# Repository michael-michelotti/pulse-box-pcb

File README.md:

# Pulse Box PCB

KiCad 9.0 hardware designs for the [PulseBox](https://github.com/michael-michelotti/pulse-box-esp) project — a modular LED grid system with a central controller driving a dynamically reconfigurable array of 8x8 LED panels. This repo holds the schematics, board layouts, and JLCPCB manufacturing outputs for all board revisions.

This is meant as a companion to the [main PulseBox repo](https://github.com/michael-michelotti/pulse-box-esp) — see that repo for the full system overview.

---

## Controller v1 (`Pulse_Box_PCB_v1/`)

<!-- TODO: Replace with labeled photo of v1 controller board -->

Original controller, fabricated and assembled by JLCPCB. 2-layer board built around an **STM32F407VGT6** (ARM Cortex-M4, LQFP-100). Power comes in through a 5.5mm barrel jack and is regulated by a **TPSM53604RDA** 4A buck module (down to 5V), followed by an **AP2112K-3.3** LDO for the 3.3V MCU rail. LED data is level-shifted from 3.3V to 5V through a **SN74LV1T34** before driving the WS2812B chain. USB Micro-B for serial/flashing.

---

## Controller v2 (`Pulse_Box_PCB_v2/`)

<!-- TODO: Replace with labeled photo of v2 controller board -->

Redesigned controller centered on the **ESP32-S3-WROOM-1** module (WiFi, BLE, dual-core). 2-layer, 80mm x 80mm. The barrel jack is replaced with a 24V input to match the rest of the panel bus, and the buck module is swapped for a **discrete TPS54560B** design (24V→5V, 5A) with an **AP2112K-3.3** LDO for the 3.3V rail. USB-C exposes the ESP32-S3's native USB-JTAG for debug. Dual **SN74LV1T34** level shifters drive LED data north and west, and panel interconnect is 8-pin (24V, GND, RS-485 A/B, sense, LED data).

---

## Panel v1 (`Pulse_Box_Panel_v1/`)

<!-- TODO: Replace with labeled photo of panel board -->

LED panel board, 2-layer, 80mm x 80mm. Runs an **STM32G071C8** (Cortex-M0+, LQFP-48) with four USARTs — one per edge — so adjacent panels mate face-to-face with no crossover. Power mirrors the v2 controller: 24V bus in, discrete buck to 5V for the LEDs, **AP2112K-3.3** LDO for the 3.3V MCU rail. LED data routing uses two **74HC4051** 8-channel analog muxes (one for input, one for output) so any edge can be selected as the data in/out for the panel's 8x8 grid. Four JST XH 11-position edge connectors carry 24V, GND, UART TX/RX, sense, and LED data. SWD header for debug; UART bootloader available on PA2/PA3 as a recovery path.

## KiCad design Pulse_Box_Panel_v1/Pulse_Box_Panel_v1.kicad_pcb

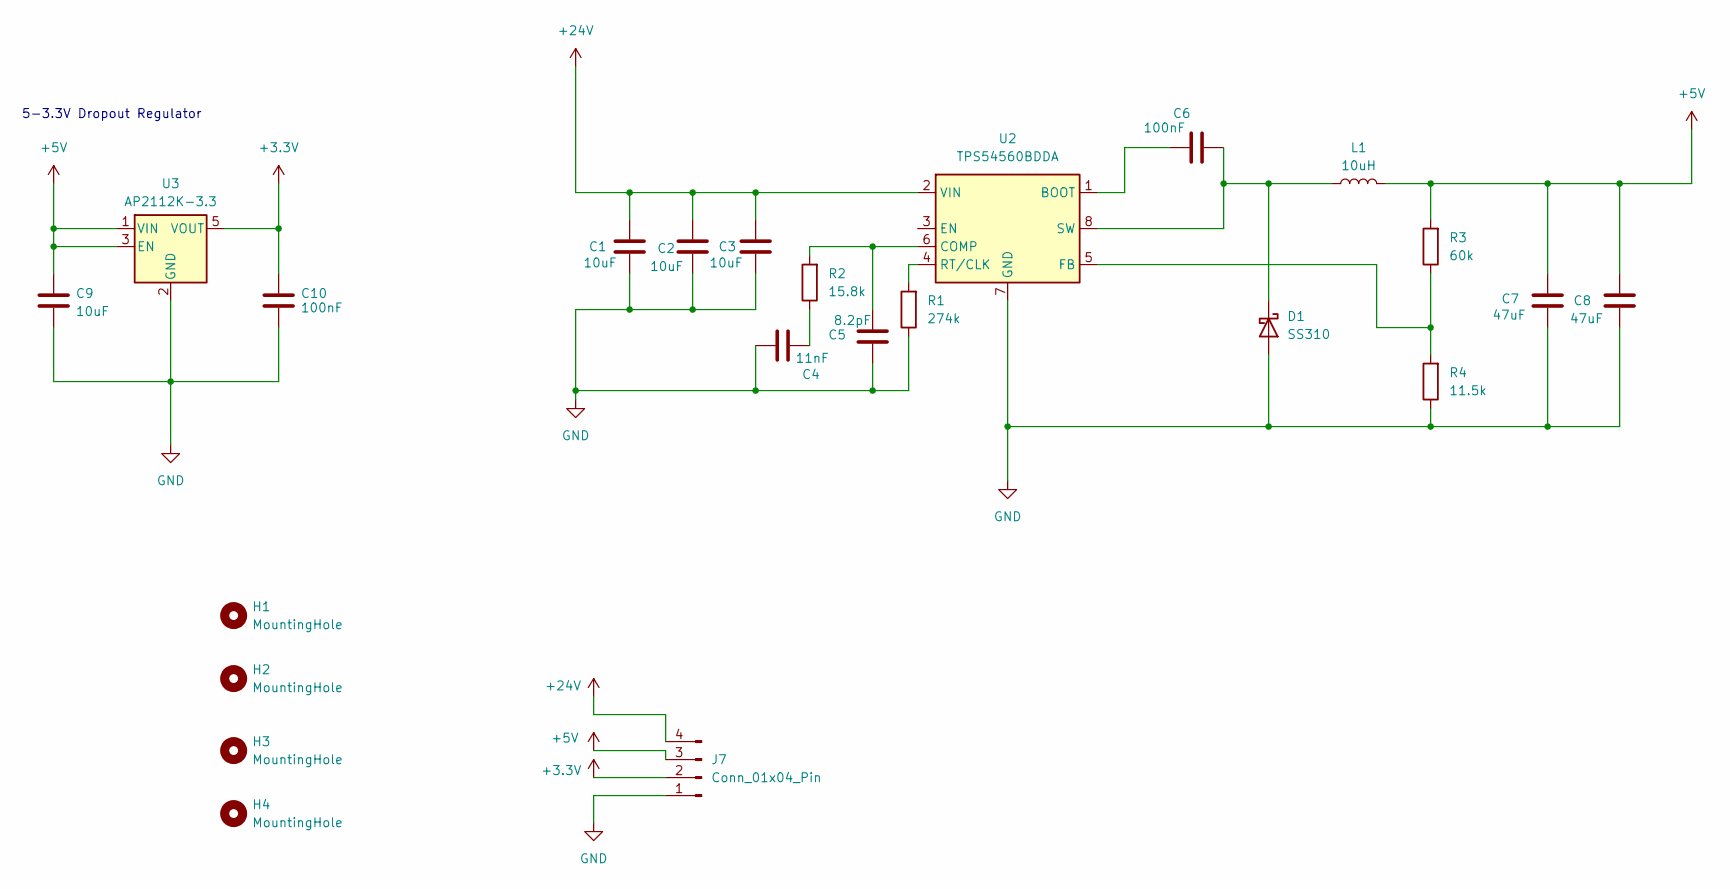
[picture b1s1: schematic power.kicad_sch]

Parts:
C1, C2, C3: 10uF; C_0805_2012Metric; JLCPCB Part # C440198
C4: 11nF; C_0805_2012Metric; JLCPCB Part # C710944
C5: 8.2pF; C_0402_1005Metric; JLCPCB Part # C1579
C6: 100nF; C_0402_1005Metric; JLCPCB Part # C1525
C7, C8: 47uF; C_0805_2012Metric; JLCPCB Part # C76636
C9: 10uF; C_0805_2012Metric; MFR PN CL21A106KAYNNNE; JLCPCB PN C15850
C10: 100nF; C_0402_1005Metric; MFR PN CL21A475KAQNNNE; JLCPCB PN C1779
D1: SS310; D_SMB; JLCPCB Part # C14651
H1, H2, H3, H4: MountingHole; MountingHole_3.2mm_M3
J7: Conn_01x04_Pin; PinHeader_1x04_P2.54mm_Vertical; JLCPCB Part # C124378
L1: 10uH; L_TechFuse_SL1040; JLCPCB Part # C22463839
R1: 274k; R_0402_1005Metric; JLCPCB Part # C27004
R2: 15.8k; R_0402_1005Metric; JLCPCB Part # C26956
R3: 60k; R_0402_1005Metric; JLCPCB Part # C25911
R4: 11.5k; R_0402_1005Metric; JLCPCB Part # C159139
U2: TPS54560BDDA; Texas_R-PDSO-G8_EP2.95x4.9mm_Mask2.4x3.1mm_ThermalVias; JLCPCB Part # C1850354
U3: AP2112K-3.3; SOT-23-5; MFR PN AP2112K-3.3; JLCPCB PN C23380830

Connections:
+3.3V: C10.1, J7.2, U3.5 (VOUT); also elsewhere on the board
+5V: C7.1, C8.1, C9.1, J7.3, L1.2, R3.2, U3.1 (VIN), U3.3 (EN); also elsewhere on the board
+24V: C1.1, C2.1, C3.1, J7.4, U2.2 (VIN); also elsewhere on the board
GND: C1.2, C2.2, C3.2, C4.1, C5.2, C7.2, C8.2, C9.2, C10.2, D1.2 (A), J7.1, R1.1, R4.1, U2.7 (GND), U2.9 (GND), U3.2 (GND); also elsewhere on the board
unnamed: C4.2, R2.1
unnamed: C6.2, D1.1 (K), L1.1, U2.8 (SW)
unnamed: C6.1, U2.1 (BOOT)
unnamed: C5.1, R2.2, U2.6 (COMP)
unnamed: R3.1, R4.2, U2.5 (FB)
unnamed: R1.2, U2.4 (RT/CLK)

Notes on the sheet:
5-3.3V Dropout Regulator

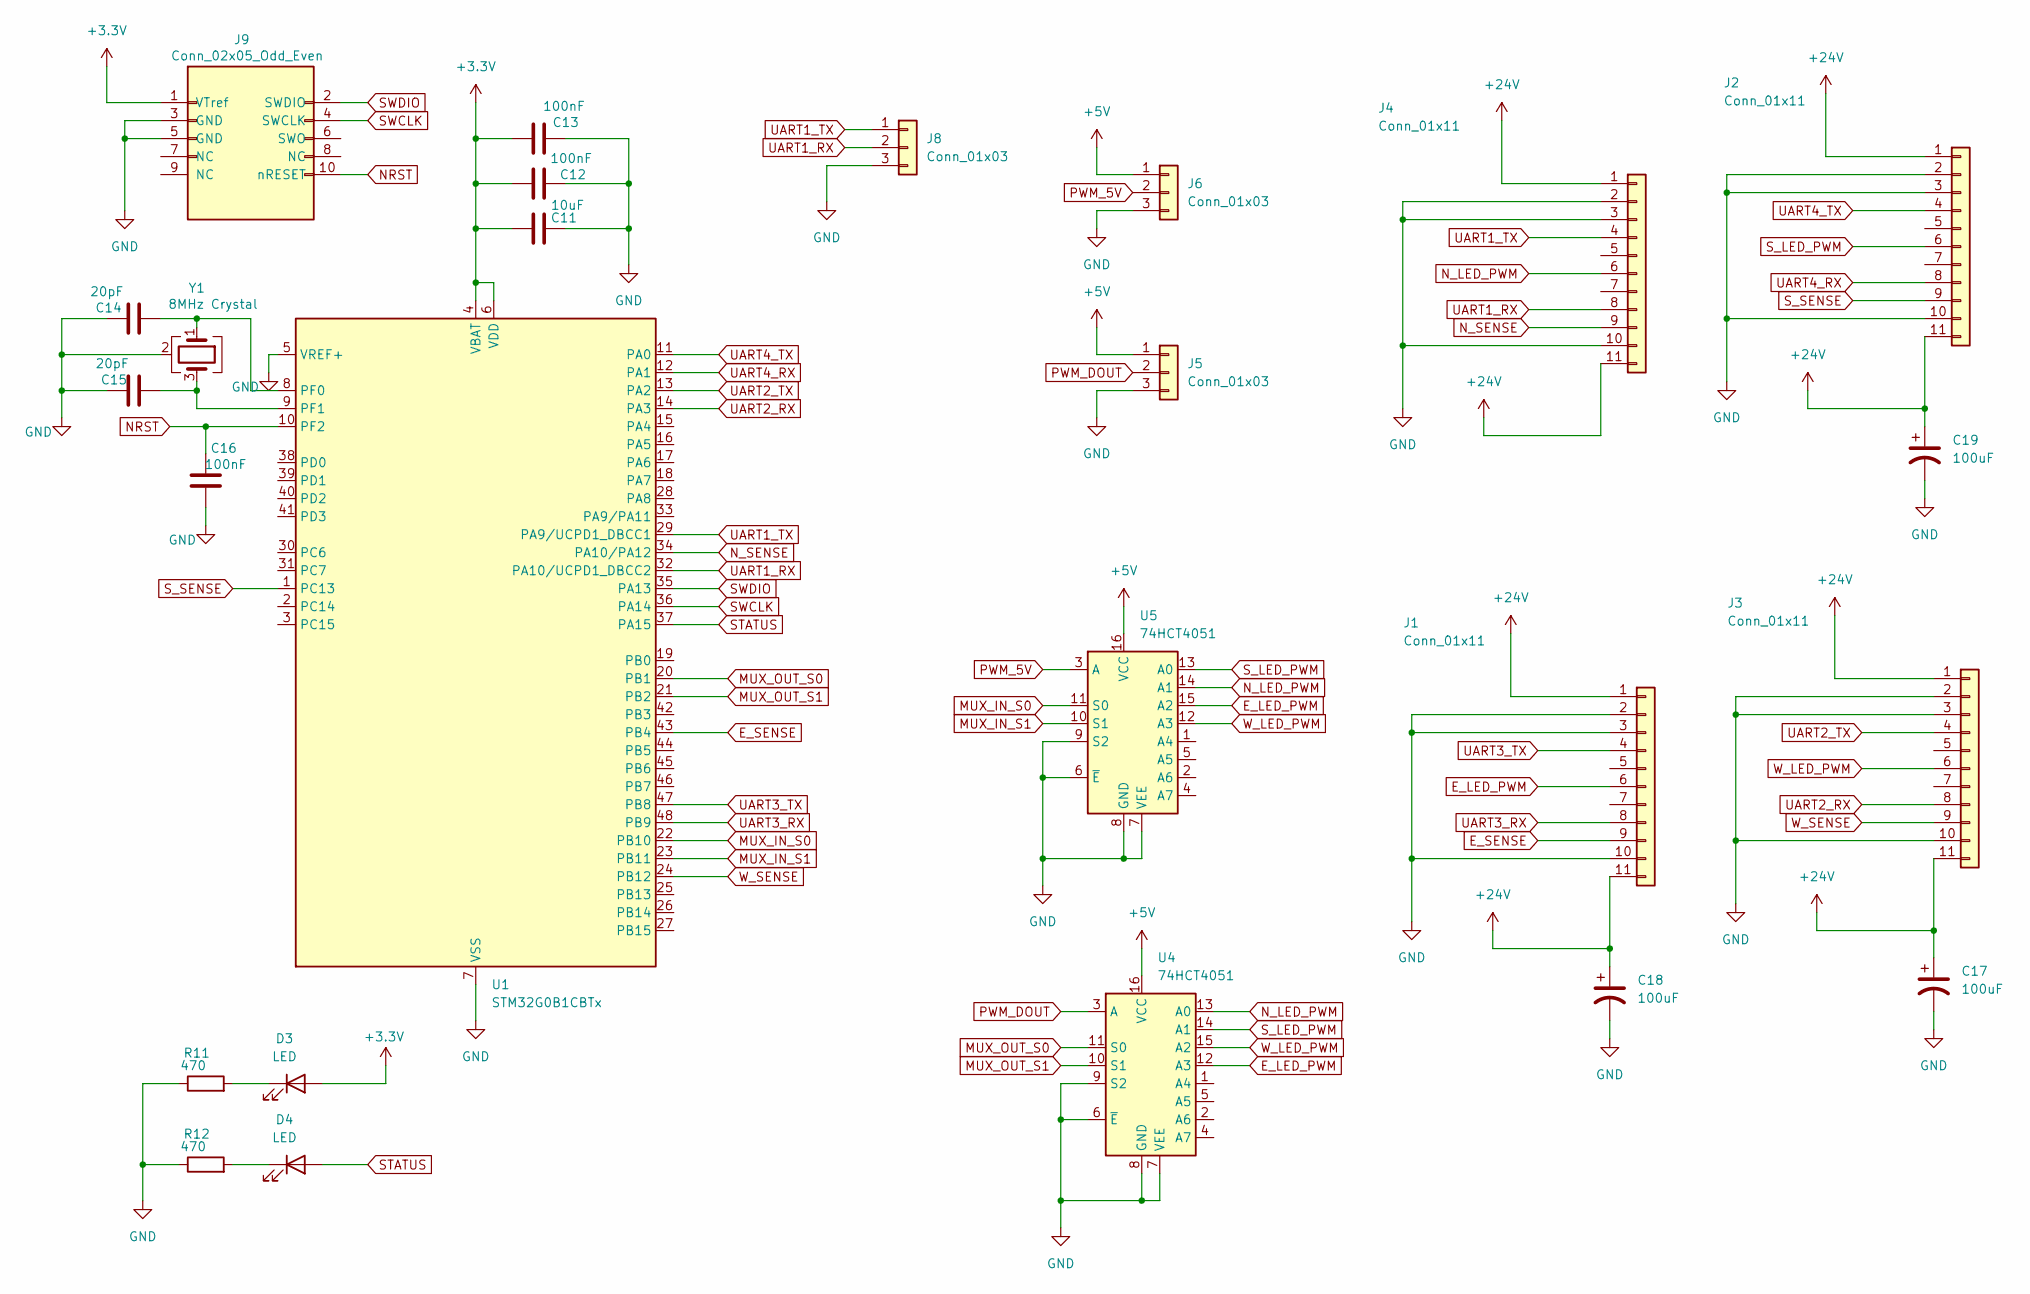
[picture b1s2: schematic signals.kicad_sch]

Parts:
C11: 10uF; C_0805_2012Metric; JLCPCB Part # C440198
C12, C13, C16: 100nF; C_0402_1005Metric; JLCPCB Part # C1525
C14, C15: 20pF; C_0402_1005Metric; JLCPCB Part # C1554
C17, C18, C19: 100uF; C_Elec_8x10.2; JLCPCB Part # C3352
D3, D4: LED; LED_0402_1005Metric; JLCPCB Part # C71911
J1, J2, J3, J4: Conn_01x11; JST_XH_B11B-XH-A_1x11_P2.50mm_Vertical; JLCPCB Part # C158031
J5, J6: Conn_01x03; JST_PH_B3B-PH-K_1x03_P2.00mm_Vertical; JLCPCB Part # C131339
J8: Conn_01x03; PinHeader_1x03_P2.54mm_Vertical; JLCPCB Part # C49257
J9: Conn_02x05_Odd_Even; PinHeader_2x05_P1.27mm_Vertical; MFR PN 20021111-00010T4LF; JLCPCB PN C239059
R11, R12: 470; R_0402_1005Metric; JLCPCB Part # C25117
U1: STM32G0B1CBTx; LQFP-48_7x7mm_P0.5mm; JLCPCB Part # C529341
U4, U5: 74HCT4051; TSSOP-16_4.4x5mm_P0.65mm; JLCPCB Part # C192055
Y1: 8MHz Crystal; Crystal_SMD_3225-4Pin_3.2x2.5mm; MFR PN 1C208000BC0R; JLCPCB PN C57131

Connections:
+3.3V: C11.1, C12.1, C13.1, D3.2 (A), J9.1 (VTref), U1.4 (VBAT), U1.6 (VDD); also elsewhere on the board
+5V: J5.1, J6.1, U4.16 (VCC), U5.16 (VCC); also elsewhere on the board
+24V: C17.1, C18.1, C19.1, J1.1, J1.11, J2.1, J2.11, J3.1, J3.11, J4.1, J4.11; also elsewhere on the board
E_LED_PWM: J1.6, U4.12 (A3), U5.15 (A2)
E_SENSE: J1.9, U1.43 (PB4)
GND: C11.2, C12.2, C13.2, C14.1, C15.1, C16.1, C17.2, C18.2, C19.2, J1.2, J1.3, J1.10, J2.2, J2.3, J2.10, J3.2, J3.3, J3.10, J4.2, J4.3, J4.10, J5.3, J6.3, J8.3, J9.3 (GND), J9.5 (GND), R11.1, R12.1, U1.5 (VREF+), U1.7 (VSS), U4.6 (~E), U4.7 (VEE), U4.8 (GND), U4.9 (S2), U5.6 (~E), U5.7 (VEE), U5.8 (GND), U5.9 (S2), Y1.2 (G), Y1.4 (G); also elsewhere on the board
MUX_IN_S0: U1.22 (PB10), U5.11 (S0)
MUX_IN_S1: U1.23 (PB11), U5.10 (S1)
MUX_OUT_S0: U1.20 (PB1), U4.11 (S0)
MUX_OUT_S1: U1.21 (PB2), U4.10 (S1)
NRST: C16.2, J9.10 (nRESET), U1.10 (PF2)
N_LED_PWM: J4.6, U4.13 (A0), U5.14 (A1)
N_SENSE: J4.9, U1.34 (PA10/PA12)
unnamed: D3.1 (K), R11.2
unnamed: D4.1 (K), R12.2
unnamed: C14.2, U1.8 (PF0), Y1.1
unnamed: C15.2, U1.9 (PF1), Y1.3
PWM_5V: J6.2, U5.3 (A)
PWM_DOUT: J5.2, U4.3 (A)
STATUS: D4.2 (A), U1.37 (PA15)
SWCLK: J9.4 (SWCLK), U1.36 (PA14)
SWDIO: J9.2 (SWDIO), U1.35 (PA13)
S_LED_PWM: J2.6, U4.14 (A1), U5.13 (A0)
S_SENSE: J2.9, U1.1 (PC13)
UART1_RX: J4.8, J8.2, U1.32 (PA10/UCPD1_DBCC2)
UART1_TX: J4.4, J8.1, U1.29 (PA9/UCPD1_DBCC1)
UART2_RX: J3.8, U1.14 (PA3)
UART2_TX: J3.4, U1.13 (PA2)
UART3_RX: J1.8, U1.48 (PB9)
UART3_TX: J1.4, U1.47 (PB8)
UART4_RX: J2.8, U1.12 (PA1)
UART4_TX: J2.4, U1.11 (PA0)
W_LED_PWM: J3.6, U4.15 (A2), U5.12 (A3)
W_SENSE: J3.9, U1.24 (PB12)

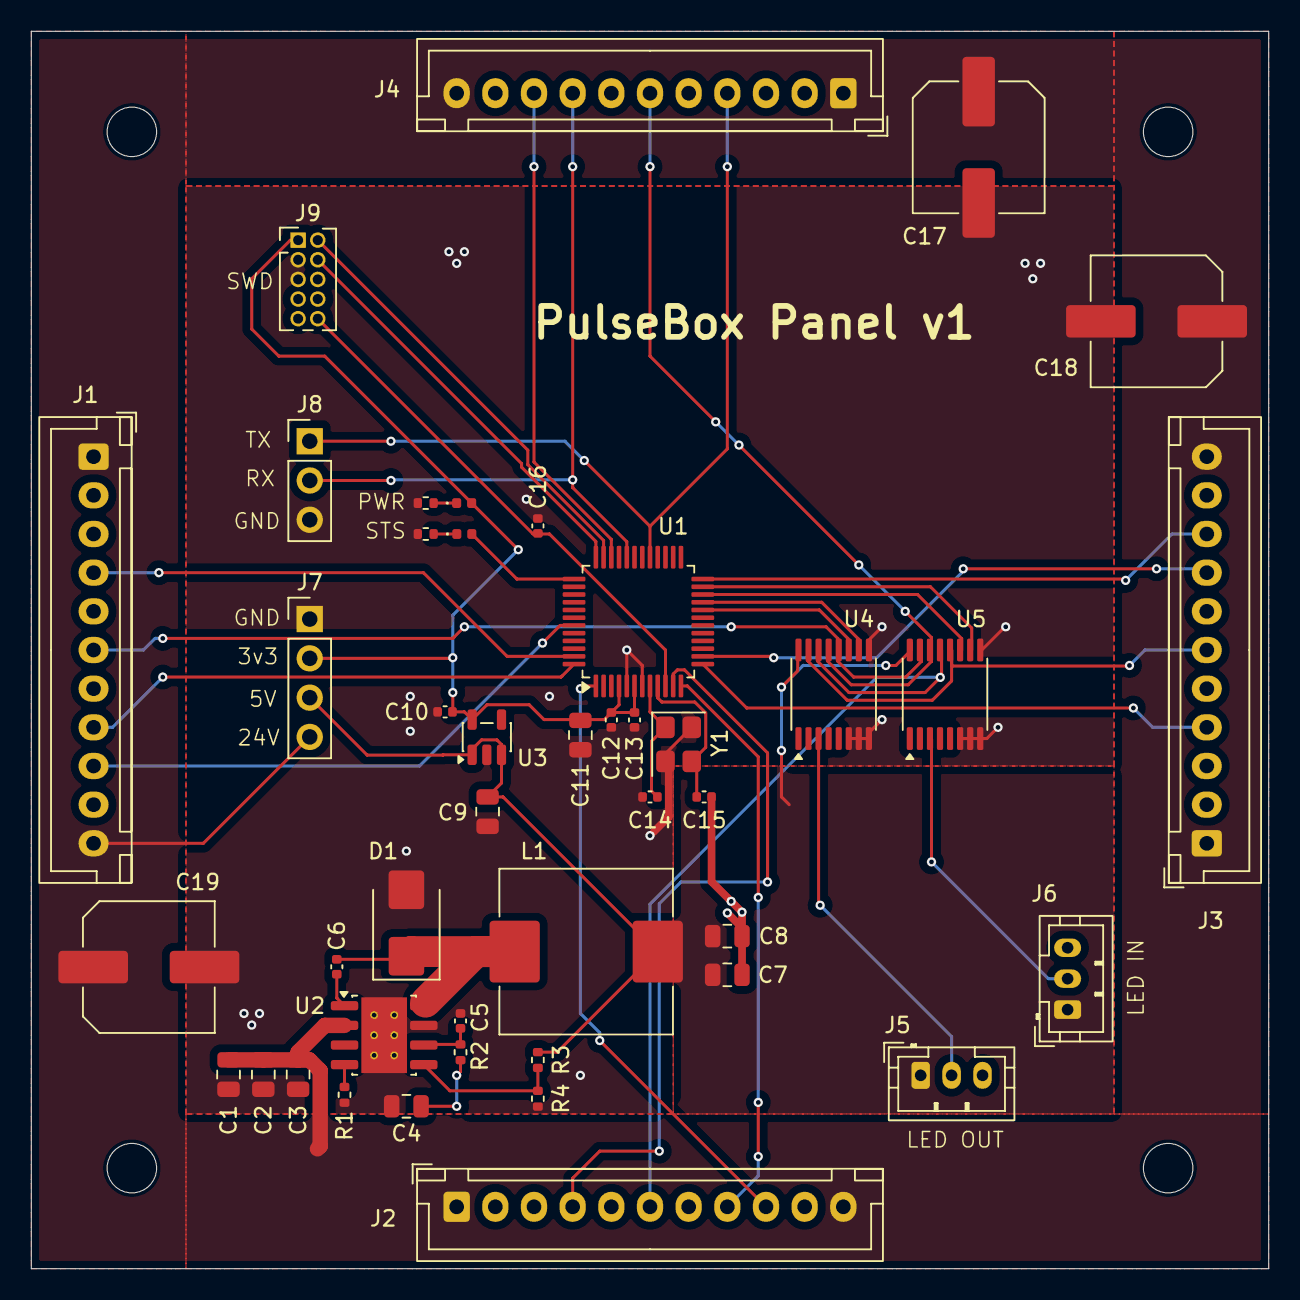
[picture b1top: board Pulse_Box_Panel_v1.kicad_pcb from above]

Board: 2 copper layers, 80.0 x 80.0 mm, 48 parts (0 on the bottom side), 40 nets.

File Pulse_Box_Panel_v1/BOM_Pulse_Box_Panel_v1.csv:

Comment,Designator,Footprint,JLCPCB Part #
10uF,"C1,C2,C3,C9,C11",Capacitor_SMD:C_0805_2012Metric,C440198
11nF,C4,Capacitor_SMD:C_0805_2012Metric,C710944
8.2pF,C5,Capacitor_SMD:C_0402_1005Metric,C1579
100nF,"C6,C10,C12,C13,C16",Capacitor_SMD:C_0402_1005Metric,C1525
47uF,"C7,C8",Capacitor_SMD:C_0805_2012Metric,C76636
20pF,"C14,C15",Capacitor_SMD:C_0402_1005Metric,C1554
100uF,"C17,C18,C19",Capacitor_SMD:C_Elec_8x10.2,C3352
SS310,D1,Diode_SMD:D_SMB,C14651
LED,"D3,D4",LED_SMD:LED_0402_1005Metric,C71911
Conn_01x11,"J1,J2,J3,J4",Connector_JST:JST_XH_B11B-XH-A_1x11_P2.50mm_Vertical,C158031
Conn_01x03,"J5,J6",Connector_JST:JST_PH_B3B-PH-K_1x03_P2.00mm_Vertical,C131339
Conn_01x04_Pin,J7,Connector_PinHeader_2.54mm:PinHeader_1x04_P2.54mm_Vertical,C124378
Conn_01x03,J8,Connector_PinHeader_2.54mm:PinHeader_1x03_P2.54mm_Vertical,C49257
Conn_02x05_Odd_Even,J9,Connector_PinHeader_1.27mm:PinHeader_2x05_P1.27mm_Vertical,C239059
10uH,L1,Inductor_SMD:L_TechFuse_SL1040,C22463839
274k,R1,Resistor_SMD:R_0402_1005Metric,C27004
15.8k,R2,Resistor_SMD:R_0402_1005Metric,C26956
60k,R3,Resistor_SMD:R_0402_1005Metric,C25911
11.5k,R4,Resistor_SMD:R_0402_1005Metric,C159139
470,"R11,R12",Resistor_SMD:R_0402_1005Metric,C25117
STM32G0B1CBTx,U1,Package_QFP:LQFP-48_7x7mm_P0.5mm,C529341
TPS54560BDDA,U2,Package_SO:Texas_R-PDSO-G8_EP2.95x4.9mm_Mask2.4x3.1mm_ThermalVias,C1850354
AP2112K-3.3,U3,Package_TO_SOT_SMD:SOT-23-5,C3021085
74HCT4051,"U4,U5",Package_SO:TSSOP-16_4.4x5mm_P0.65mm,C192055
8MHz Crystal,Y1,Crystal:Crystal_SMD_3225-4Pin_3.2x2.5mm,C57131

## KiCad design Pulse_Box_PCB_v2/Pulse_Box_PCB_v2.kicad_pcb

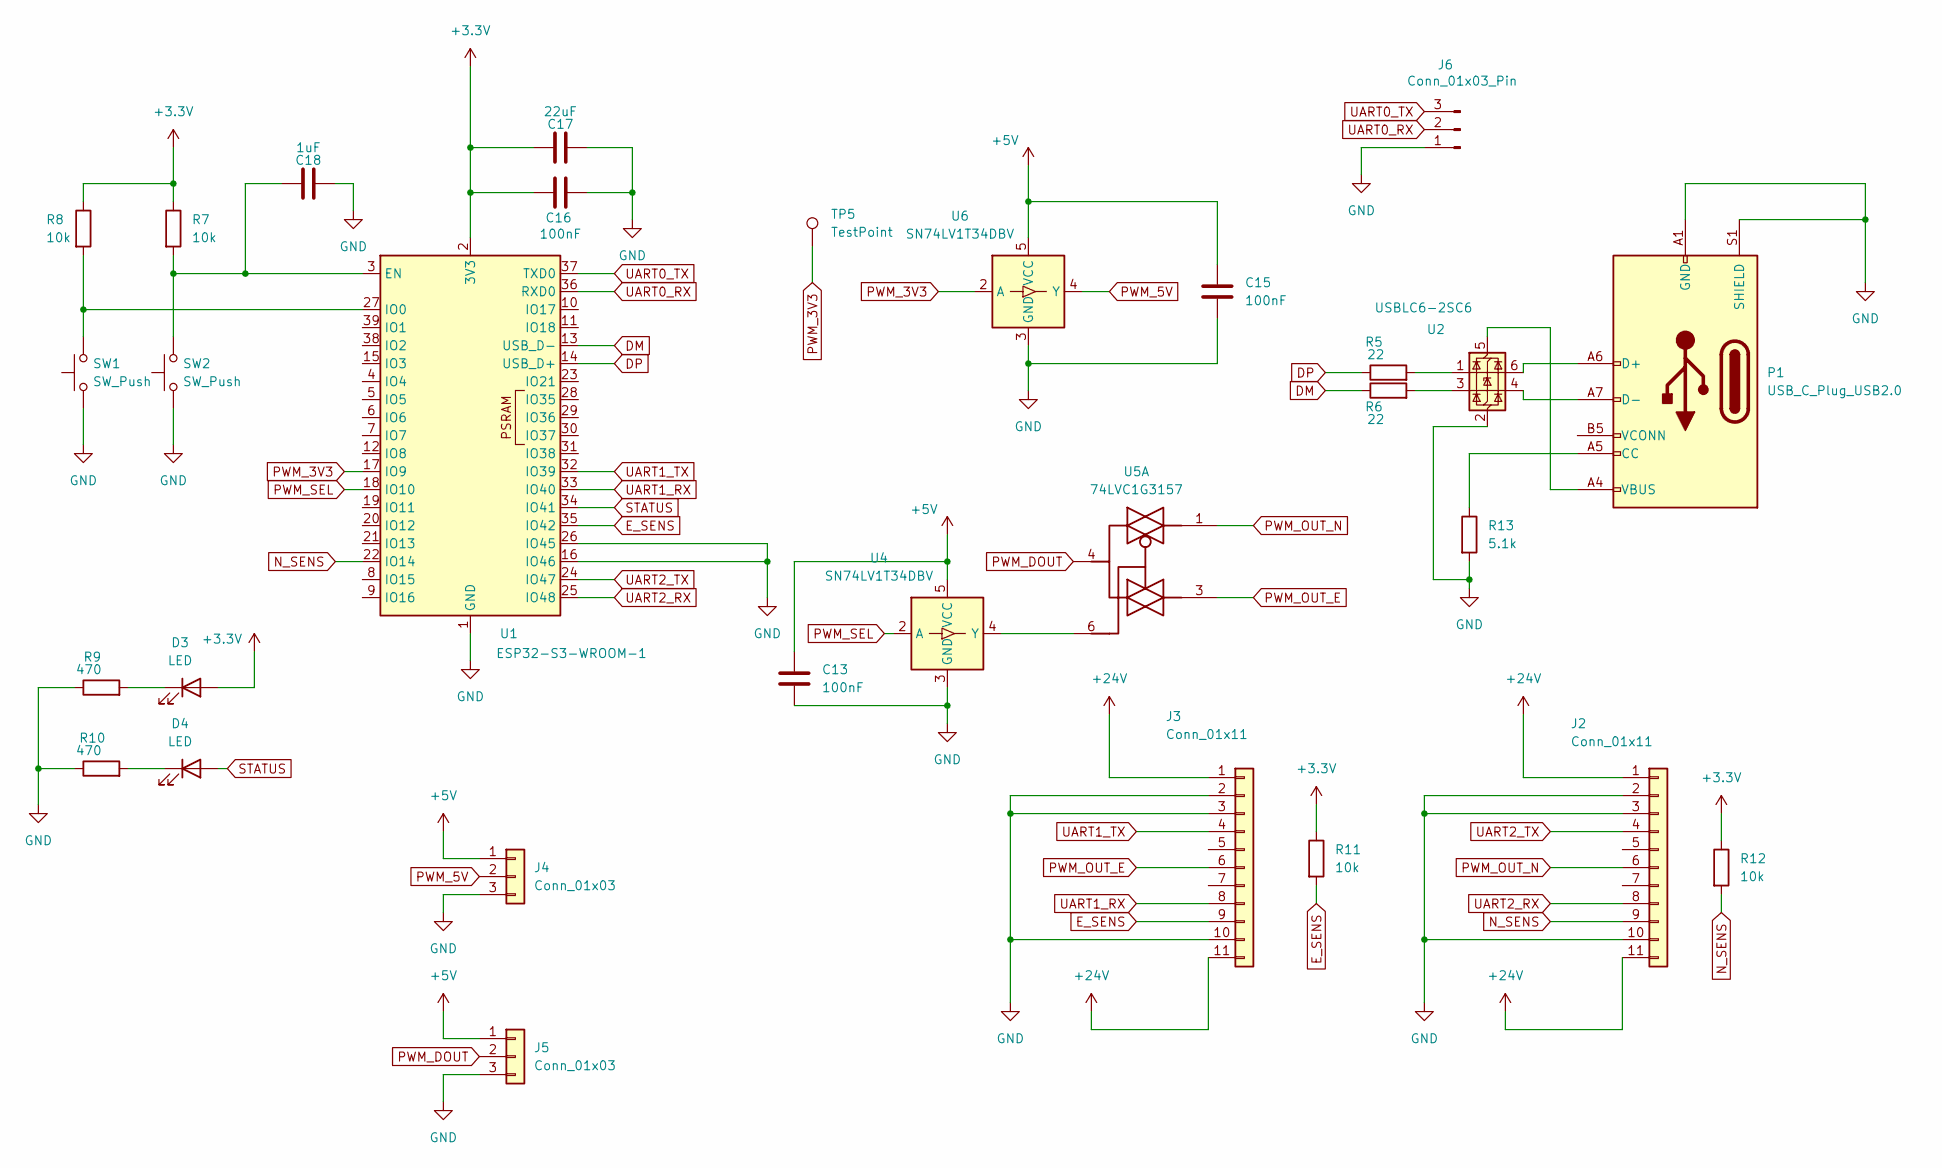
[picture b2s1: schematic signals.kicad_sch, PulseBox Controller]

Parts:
C13, C15, C16: 100nF; C_0402_1005Metric; JLCPCB Part # C1525
C17: 22uF; C_1206_3216Metric_Pad1.33x1.80mm_HandSolder; JLCPCB Part # C12891
C18: 1uF; C_0402_1005Metric; JLCPCB Part # C52923
D3, D4: LED; LED_0402_1005Metric; JLCPCB Part # C71911
J2, J3: Conn_01x11; JST_XH_B11B-XH-A_1x11_P2.50mm_Vertical; JLCPCB Part # C158031
J4, J5: Conn_01x03; JST_PH_B3B-PH-K_1x03_P2.00mm_Vertical; JLCPCB Part # C131339
J6: Conn_01x03_Pin; PinHeader_1x03_P2.54mm_Vertical; JLCPCB Part # C49257
P1: USB_C_Plug_USB2.0; USB_C_Receptacle_HRO_TYPE-C-31-M-12; JLCPCB Part # C165948
R5, R6: 22; R_0402_1005Metric; JLCPCB Part # C25092
R7, R8, R11, R12: 10k; R_0402_1005Metric; JLCPCB Part # C25744
R9, R10: 470; R_0402_1005Metric; JLCPCB Part # C25117
R13: 5.1k; R_0402_1005Metric; JLCPCB Part # C25905
SW1, SW2: SW_Push; SW_Push_SPST_NO_Alps_SKRK; JLCPCB Part # C398055
TP5: TestPoint; TestPoint_Pad_2.0x2.0mm
U1: ESP32-S3-WROOM-1; JLCPCB Part # C2913197
U2: USBLC6-2SC6; SOT-23-6; JLCPCB Part # C558442
U4, U6: SN74LV1T34DBV; SOT-23-5; JLCPCB Part # C100024
U5: 74LVC1G3157; SOT-23-6; JLCPCB Part # C10426

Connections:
+3.3V: C16.2, C17.2, D3.2 (A), R7.1, R8.1, R11.1, R12.1, U1.2 (3V3); also elsewhere on the board
+5V: C13.1, C15.1, J4.1, J5.1, U4.5 (VCC), U6.5 (VCC); also elsewhere on the board
+24V: J2.1, J2.11, J3.1, J3.11; also elsewhere on the board
DM: R6.1, U1.13 (USB_D-)
DP: R5.1, U1.14 (USB_D+)
E_SENS: J3.9, R11.2, U1.35 (IO42)
GND: C13.2, C15.2, C16.1, C17.1, C18.1, J2.2, J2.3, J2.10, J3.2, J3.3, J3.10, J4.3, J5.3, J6.1, P1.A1 (GND), P1.A12 (GND), P1.B1 (GND), P1.B12 (GND), P1.S1 (SHIELD), R9.1, R10.1, R13.2, SW1.1, SW2.1, U1.1 (GND), U1.16 (IO46), U1.26 (IO45), U1.40 (GND), U1.41 (GND), U2.2 (GND), U4.3 (GND), U6.3 (GND); also elsewhere on the board
N_SENS: J2.9, R12.2, U1.22 (IO14)
unnamed: D3.1 (K), R9.2
unnamed: D4.1 (K), R10.2
unnamed: P1.A5 (CC), R13.1
unnamed: P1.A6 (D+), U2.6 (I/O1)
unnamed: P1.A7 (D-), U2.4 (I/O2)
unnamed: R5.2, U2.1 (I/O1)
unnamed: R6.2, U2.3 (I/O2)
unnamed: C18.2, R7.2, SW2.2, U1.3 (EN)
unnamed: R8.2, SW1.2, U1.27 (IO0)
unnamed: P1.A4 (VBUS), P1.A9 (VBUS), P1.B4 (VBUS), P1.B9 (VBUS), U2.5 (VBUS)
unnamed: U4.4 (Y), U5.6
PWM_3V3: TP5.1, U1.17 (IO9), U6.2 (A)
PWM_5V: J4.2, U6.4 (Y)
PWM_DOUT: J5.2, U5.4
PWM_OUT_E: J3.6, U5.3
PWM_OUT_N: J2.6, U5.1
PWM_SEL: U1.18 (IO10), U4.2 (A)
STATUS: D4.2 (A), U1.34 (IO41)
UART0_RX: J6.2, U1.36 (RXD0)
UART0_TX: J6.3, U1.37 (TXD0)
UART1_RX: J3.8, U1.33 (IO40)
UART1_TX: J3.4, U1.32 (IO39)
UART2_RX: J2.8, U1.25 (IO48)
UART2_TX: J2.4, U1.24 (IO47)

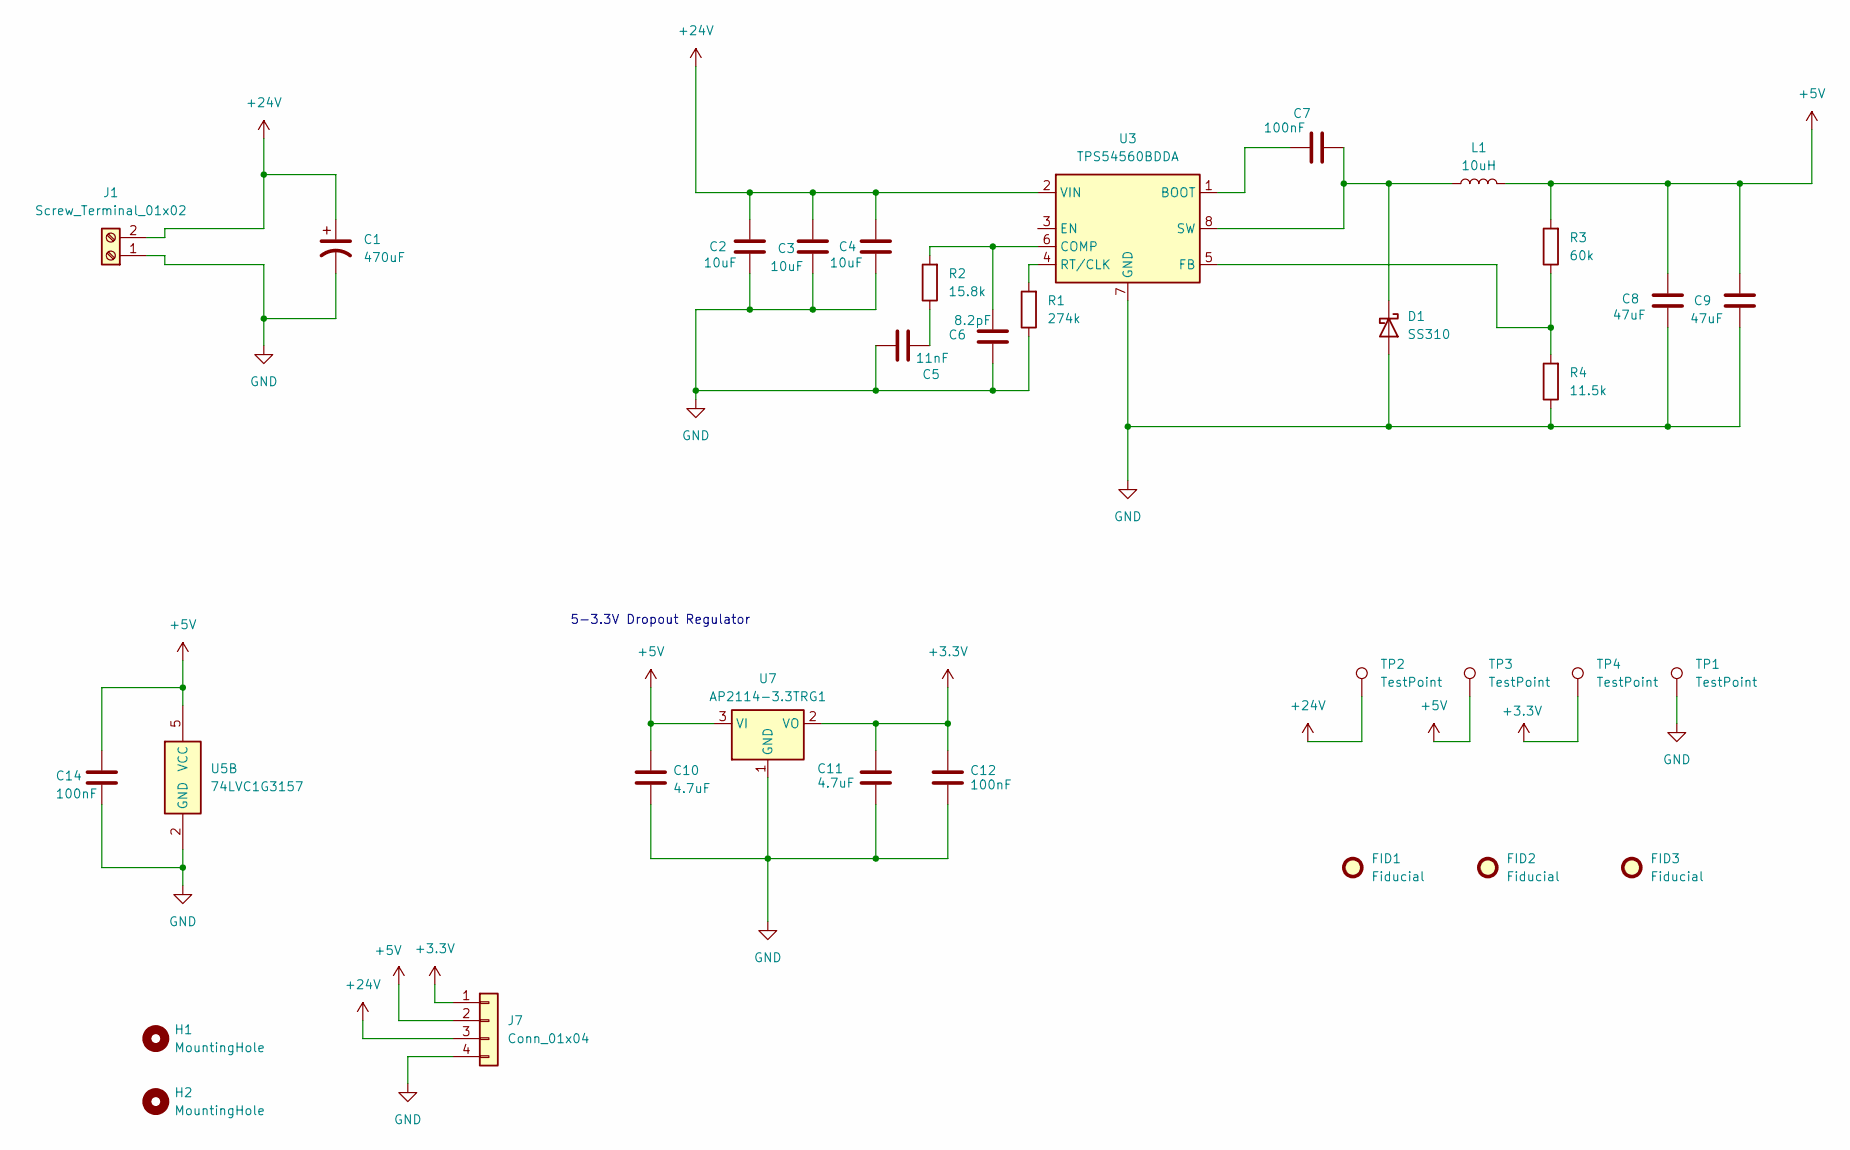
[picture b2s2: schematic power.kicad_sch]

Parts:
C1: 470uF; CP_Elec_10x12.6; JLCPCB Part # C90272
C2, C3, C4: 10uF; C_0805_2012Metric; JLCPCB Part # C440198
C5: 11nF; C_0805_2012Metric; JLCPCB Part # C710944
C6: 8.2pF; C_0402_1005Metric; JLCPCB Part # C1579
C7, C14: 100nF; C_0402_1005Metric; JLCPCB Part # C1525
C8, C9: 47uF; C_0805_2012Metric; JLCPCB Part # C76636
C10: 4.7uF; C_0805_2012Metric; MFR PN CL21A106KAYNNNE; JLCPCB PN C15850
C11: 4.7uF; C_0805_2012Metric; MFR PN CL21A475KAQNNNE; JLCPCB PN C1779
C12: 100nF; C_0402_1005Metric; MFR PN CL21A475KAQNNNE; JLCPCB PN C1779
D1: SS310; D_SMB; JLCPCB Part # C14651
FID1, FID2, FID3: Fiducial; Fiducial_0.5mm_Mask1.5mm
H1, H2: MountingHole; MountingHole_3.2mm_M3
J1: Screw_Terminal_01x02; TerminalBlock_Phoenix_MKDS-1,5-2-5.08_1x02_P5.08mm_Horizont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; JLCPCB Part # C8465
J7: Conn_01x04; PinHeader_1x04_P2.54mm_Vertical; JLCPCB Part # C124378
L1: 10uH; L_TechFuse_SL1040; JLCPCB Part # C22463839
R1: 274k; R_0402_1005Metric; JLCPCB Part # C27004
R2: 15.8k; R_0402_1005Metric; JLCPCB Part # C26956
R3: 60k; R_0402_1005Metric; JLCPCB Part # C25911
R4: 11.5k; R_0402_1005Metric; JLCPCB Part # C159139
TP1, TP2, TP3, TP4: TestPoint; TestPoint_Pad_2.0x2.0mm
U3: TPS54560BDDA; Texas_R-PDSO-G8_EP2.95x4.9mm_Mask2.4x3.1mm_ThermalVias; JLCPCB Part # C1850354
U5: 74LVC1G3157; SOT-23-6; JLCPCB Part # C10426
U7: AP2114-3.3TRG1; SOT-223-3_TabPin2; JLCPCB Part # C460314

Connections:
+3.3V: C11.1, C12.1, J7.1, TP4.1, U7.2 (VO); also elsewhere on the board
+5V: C8.1, C9.1, C10.1, C14.1, J7.2, L1.2, R3.2, TP3.1, U5.5 (VCC), U7.3 (VI); also elsewhere on the board
+24V: C1.1, C2.1, C3.1, C4.1, J1.2, J7.3, TP2.1, U3.2 (VIN); also elsewhere on the board
GND: C1.2, C2.2, C3.2, C4.2, C5.1, C6.2, C8.2, C9.2, C10.2, C11.2, C12.2, C14.2, D1.2 (A), J1.1, J7.4, R1.1, R4.1, TP1.1, U3.7 (GND), U3.9 (GND), U5.2 (GND), U7.1 (GND); also elsewhere on the board
unnamed: C5.2, R2.1
unnamed: C7.2, D1.1 (K), L1.1, U3.8 (SW)
unnamed: C7.1, U3.1 (BOOT)
unnamed: C6.1, R2.2, U3.6 (COMP)
unnamed: R3.1, R4.2, U3.5 (FB)
unnamed: R1.2, U3.4 (RT/CLK)

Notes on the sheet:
5-3.3V Dropout Regulator

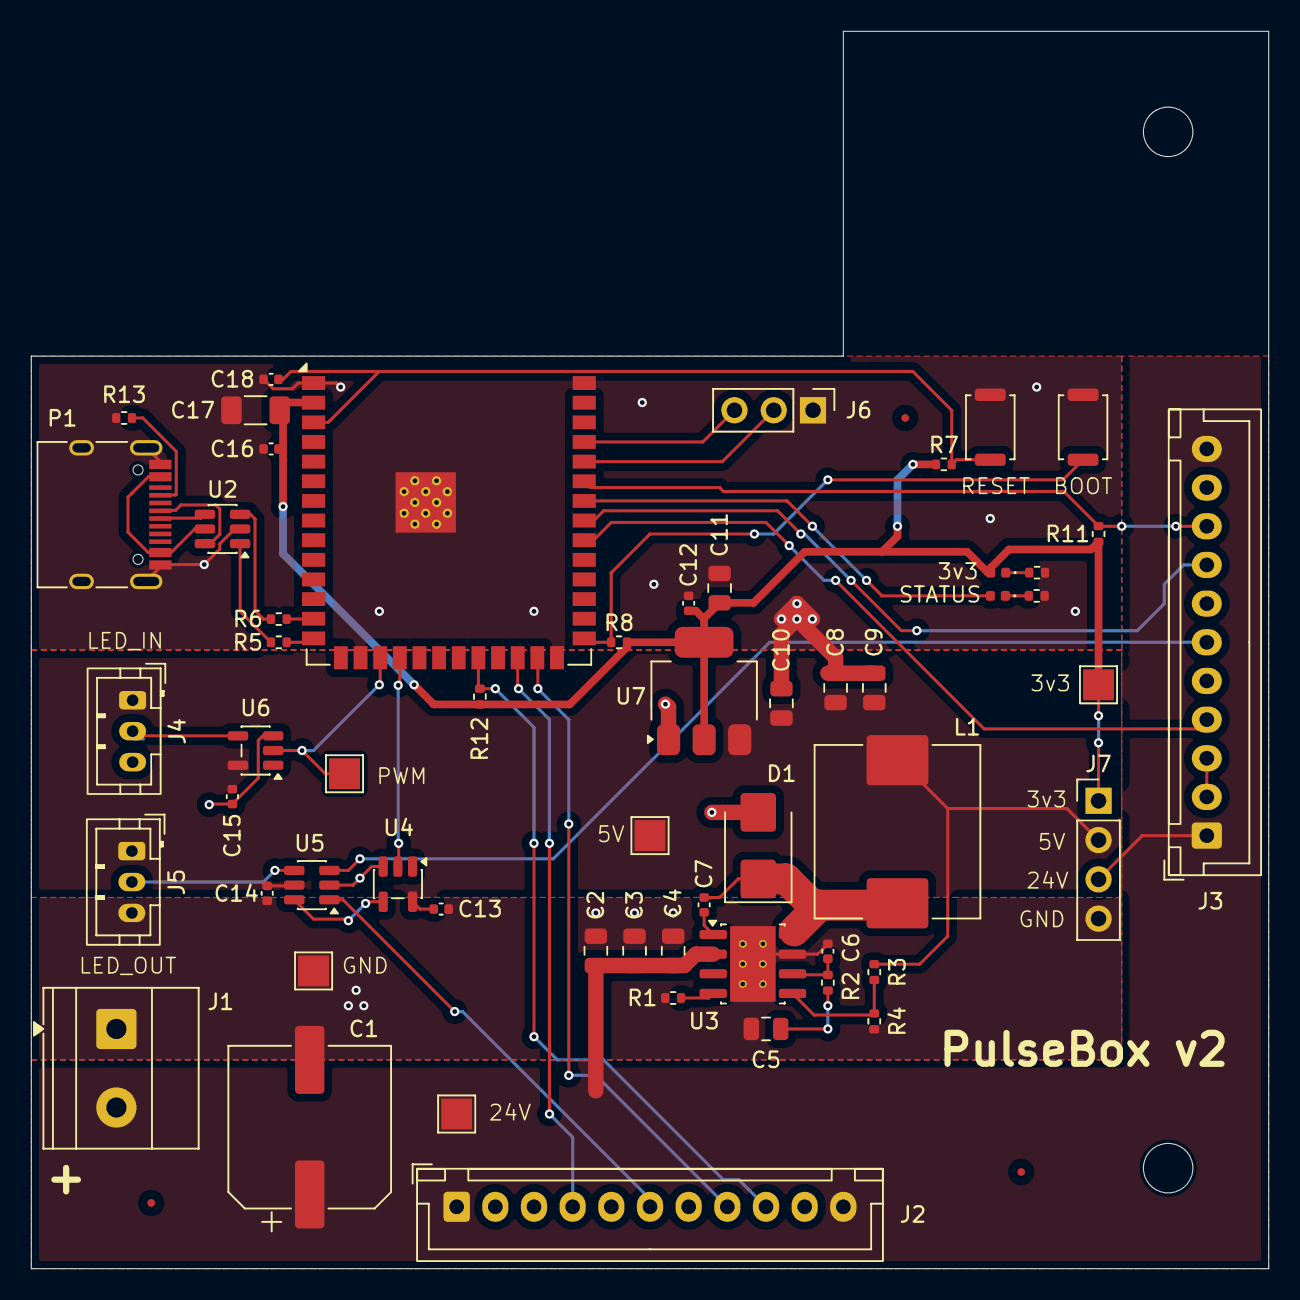
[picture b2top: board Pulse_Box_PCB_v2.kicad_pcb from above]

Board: 2 copper layers, 80.0 x 80.0 mm, 62 parts (0 on the bottom side), 38 nets.

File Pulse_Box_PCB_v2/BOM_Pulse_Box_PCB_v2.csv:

Comment,Designator,Footprint,JLCPCB Part #
470uF,C1,Capacitor_SMD:CP_Elec_10x12.6,C90272
10uF,"C2,C3,C4",Capacitor_SMD:C_0805_2012Metric,C440198
11nF,C5,Capacitor_SMD:C_0805_2012Metric,C710944
8.2pF,C6,Capacitor_SMD:C_0402_1005Metric,C1579
100nF,"C7,C12,C13,C14,C15,C16",Capacitor_SMD:C_0402_1005Metric,C1525
47uF,"C8,C9",Capacitor_SMD:C_0805_2012Metric,C76636
4.7uF,"C10,C11",Capacitor_SMD:C_0805_2012Metric,C1779
22uF,C17,Capacitor_SMD:C_1206_3216Metric_Pad1.33x1.80mm_HandSolder,C12891
1uF,C18,Capacitor_SMD:C_0402_1005Metric,C52923
SS310,D1,Diode_SMD:D_SMB,C14651
LED,"D3,D4",LED_SMD:LED_0402_1005Metric,C71911
Screw_Terminal_01x02,J1,"TerminalBlock_Phoenix:TerminalBlock_Phoenix_MKDS-1,5-2-5.08_1x02_P5.08mm_Horizontal",C8465
Conn_01x11,"J2,J3",Connector_JST:JST_XH_B11B-XH-A_1x11_P2.50mm_Vertical,C158031
Conn_01x03,"J4,J5",Connector_JST:JST_PH_B3B-PH-K_1x03_P2.00mm_Vertical,C131339
Conn_01x03_Pin,J6,Connector_PinHeader_2.54mm:PinHeader_1x03_P2.54mm_Vertical,C49257
Conn_01x04,J7,Connector_PinHeader_2.54mm:PinHeader_1x04_P2.54mm_Vertical,C124378
10uH,L1,Inductor_SMD:L_TechFuse_SL1040,C22463839
USB_C_Plug_USB2.0,P1,Connector_USB:USB_C_Receptacle_HRO_TYPE-C-31-M-12,C165948
274k,R1,Resistor_SMD:R_0402_1005Metric,C27004
15.8k,R2,Resistor_SMD:R_0402_1005Metric,C26956
60k,R3,Resistor_SMD:R_0402_1005Metric,C25911
11.5k,R4,Resistor_SMD:R_0402_1005Metric,C159139
22,"R5,R6",Resistor_SMD:R_0402_1005Metric,C25092
10k,"R7,R8,R11,R12",Resistor_SMD:R_0402_1005Metric,C25744
470,"R9,R10",Resistor_SMD:R_0402_1005Metric,C25117
5.1k,R13,Resistor_SMD:R_0402_1005Metric,C25905
SW_Push,"SW1,SW2",Button_Switch_SMD:SW_Push_SPST_NO_Alps_SKRK,C398055
ESP32-S3-WROOM-1,U1,RF_Module:ESP32-S3-WROOM-1,C2913197
USBLC6-2SC6,U2,Package_TO_SOT_SMD:SOT-23-6,C558442
TPS54560BDDA,U3,Package_SO:Texas_R-PDSO-G8_EP2.95x4.9mm_Mask2.4x3.1mm_ThermalVias,C1850354
SN74LV1T34DBV,"U4,U6",Package_TO_SOT_SMD:SOT-23-5,C100024
74LVC1G3157,U5,Package_TO_SOT_SMD:SOT-23-6,C10426
AP2114-3.3TRG1,U7,Package_TO_SOT_SMD:SOT-223-3_TabPin2,C460314

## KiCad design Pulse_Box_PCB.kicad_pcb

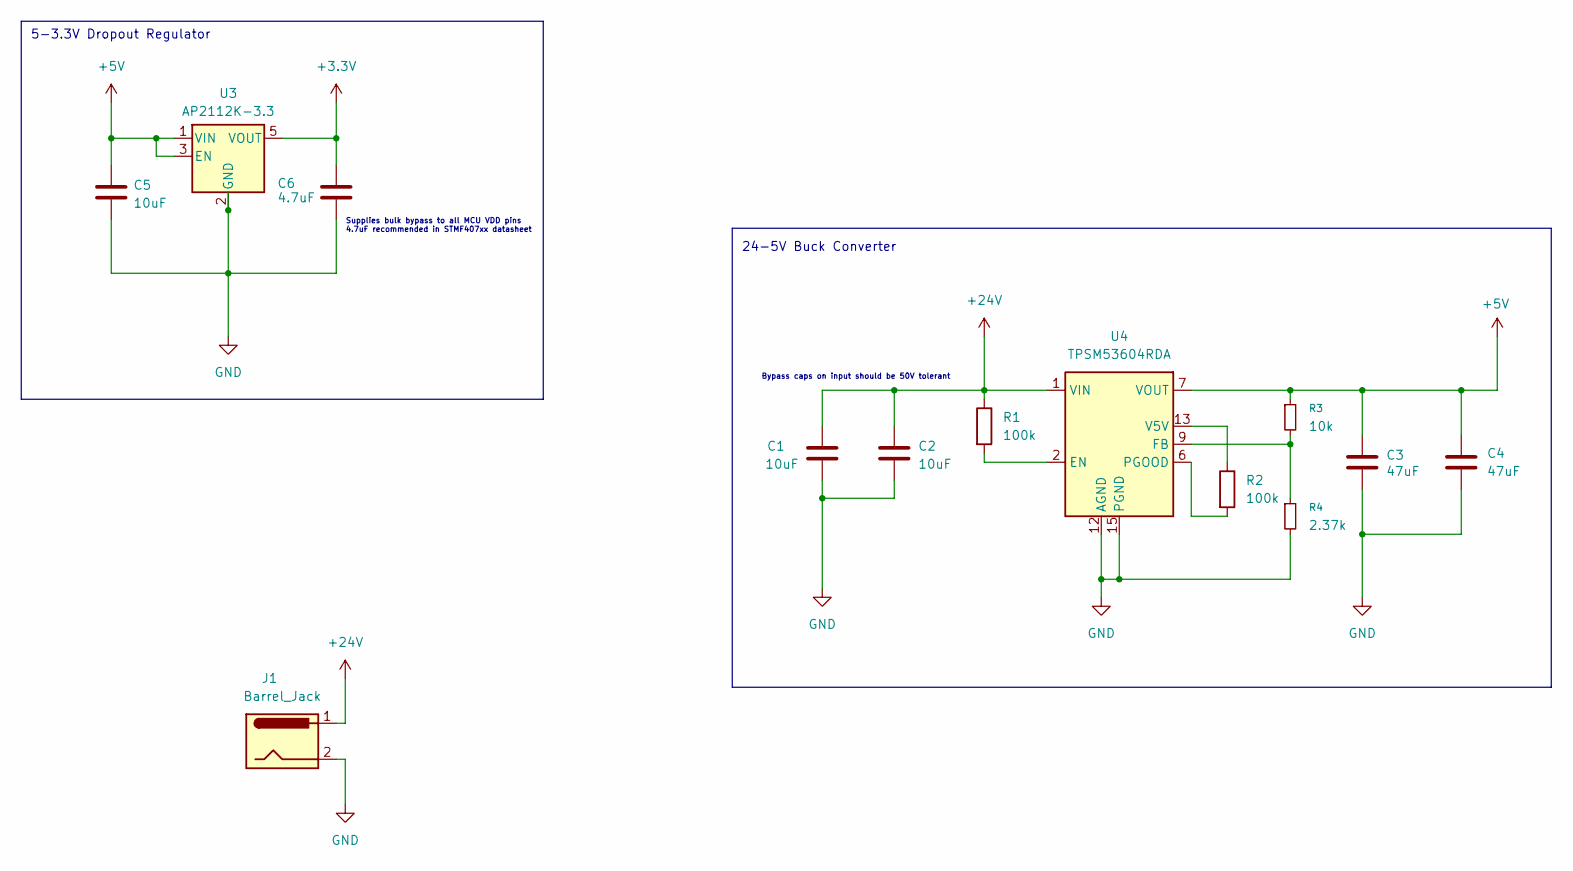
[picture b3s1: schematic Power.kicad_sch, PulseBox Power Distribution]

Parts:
C1, C2, C5: 10uF; C_0805_2012Metric; MFR PN CL21A106KAYNNNE; JLCPCB PN C15850
C3, C4: 47uF; C_1210_3225Metric; MFR PN GRM32ER61C476KE15L; JLCPCB PN C77101
C6: 4.7uF; C_0805_2012Metric; MFR PN CL21A475KAQNNNE; JLCPCB PN C1779
J1: Barrel_Jack; XKB_DC-005-5A-2.0; MFR PN DC-005-5A-2.0; JLCPCB PN C381116
R1, R2: 100k; R_0402_1005Metric; MFR PN 0402WGF1003TCE; JLCPCB PN C25741
R3: 10k; R_0402_1005Metric; MFR PN 0402WGF1002TCE; JLCPCB PN C25744
R4: 2.37k; R_0402_1005Metric; MFR PN RC0402FR-072K37L; JLCPCB PN C294439
U3: AP2112K-3.3; SOT-23-5; MFR PN AP2112K-3.3; JLCPCB PN C23380830
U4: TPSM53604RDA; Texas_B3QFN-14-1EP_5x5.5mm_P0.65mm_ThermalVia; MFR PN TPSM53604; JLCPCB PN C2868001

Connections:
+3.3V: C6.1, U3.5 (VOUT); also elsewhere on the board
+5V: C3.1, C4.1, C5.1, R3.1, U3.1 (VIN), U3.3 (EN), U4.7 (VOUT), U4.8 (VOUT); also elsewhere on the board
+24V: C1.1, C2.1, J1.1, R1.1, U4.1 (VIN), U4.14 (VIN); also elsewhere on the board
GND: C1.2, C2.2, C3.2, C4.2, C5.2, C6.2, J1.2, R4.2, U3.2 (GND), U4.3 (PGND), U4.10 (PGND), U4.11 (PGND), U4.12 (AGND), U4.15 (PGND); also elsewhere on the board
unnamed: R1.2, U4.2 (EN)
unnamed: R3.2, R4.1, U4.9 (FB)
unnamed: R2.2, U4.6 (PGOOD)
unnamed: R2.1, U4.13 (V5V)

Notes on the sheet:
5-3.3V Dropout Regulator
Bypass caps on input should be 50V tolerant
24-5V Buck Converter
Supplies bulk bypass to all MCU VDD pins 4.7uF recommended in STMF407xx datasheet
